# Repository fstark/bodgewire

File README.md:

# Bodgewire

A game about fixing old digital computers, chip by chip.

All the code in this repository was generated by Claude, Anthropic's AI, with a human telling it
what to build and checking the result. If you'd rather stay away from AI-made projects, this is
the place to stop reading. No hard feelings.

Try it in your browser: [fstark.github.io/bodgewire](https://fstark.github.io/bodgewire/).
Every Machine is there, slower than the desktop build (a fast computer helps), and without the
pop-out windows. It's not really playable that way, but it gives a good idea of what the game
looks like.

## The goal

Bodgewire simulates the repair of old digital computers: late-70s and early-80s boards made of
TTL chips, up to real 8-bit computers. Every signal on the board is simulated, so a fault is a
physical thing (a cracked trace, a chip output stuck low, a solder bridge) and the symptoms come
out of the circuit on their own. Nothing is scripted. Every fault has a cause, and you can find it.

## What it is

You're at a repair bench. In front of you is a broken Machine and a post-it saying what's wrong
with it: "The LED never lights." You have the board, its manuals (a User Manual, a Service Manual,
datasheets for every chip) and a shelf of real tools and instruments. Find the fault, fix it,
power it back on.

There are 125 Puzzles on 14 Machines. The first one blinks an LED with five chips. The last two
are chip-for-chip copies of the Commodore PET 2001 and the Sinclair ZX80, running their real ROMs.

Every Machine shows up in the launcher with a short description, and each of its Puzzles is a
post-it you can pick. "Start the Machine" gives you the working one, to see how it should behave.
A Puzzle you've repaired keeps its tick on the launcher, from one launch to the next.
The last post-it, "Random fault", breaks the Machine somewhere new each time you open it, and
checks that the fault shows before handing you the bench. It can be anywhere on the board, so
they never run out: fix one and the owner's card offers you another. If one beats you, the
binder's Give up page tells you what it was.

## A repair, step by step

Here's the Counter's first Puzzle, "Dark LED".

The bench opens on the board. Five 74LS161 counters divide a 1 MHz crystal down to about one blink
a second, and the red LED `D1` on the right should be blinking. It stays dark. The tools are on
the shelf at the bottom.

Hover a chip and its traces light up, with every pin named. On `U5`, pin 11 (`QD`) is the one that
goes to the LED.

So is the chip broken, or the LED, or something in between? Power off, take the multimeter, clip
its black lead on the LED's pad and hold the red one on `U5` pin 11. It shows dashes, no beep: a
trace runs from one to the other, but they aren't connected.

Zoom in on that trace. About halfway along, there's a hairline crack right across the copper.

A crack is a job for the soldering iron: click on it and a blob of solder bridges the gap. Power
back on, and the LED blinks.

Three seconds later the owner's card says thank you, with the next Puzzle one click away, and
the post-it gets a tick. The game checks the repair itself: the Board must now build the same
circuit as the fault-free one, whichever way you fixed it.

That one is easy. Later Puzzles hide the fault behind a TV picture that rolls, a keyboard that
types the wrong letters, or a BASIC that won't start.

## Tools and instruments

The shelf is the same on every Machine.

### Tools

- **Grease pencil**: mark the board with dots, checks and crosses, to keep track of what you've
  ruled out.
- **Chip puller**: swap a chip for a new one.
- **Soldering iron**: mend a cracked trace, resolder a chip pin.
- **Cutters**: cut a trace or a wire.
- **Bodge wire**: solder a wire between two pins.

Here the first four counters have been checked off, and the trace to the LED is the suspect:

### Instruments

- **Logic probe**: touch any copper and it tells you HIGH, LOW or PULSE.
- **Logic analyzer**: clip it on chip pins (its pin / bus switch takes a whole bus), set a
  trigger, and read what happened before and after it.
- **Oscilloscope**: four channels, for when the exact timing between signals matters.
- **Multimeter**: hold on copper; volts, or continuity with the power off.

The logic analyzer on the LED computer's 6502, triggered on its first instruction fetch. The
address and data buses read as values: the processor fetches its reset vector at FFFC and FFFD
(00, F8), jumps to F800 and starts running its program.

The oscilloscope on the Test Pattern Generator's video output: a pulse for each of the grid's
vertical lines, then the line's sync pulse below.

### The binder

Every Machine comes with its manuals, in a binder. The aA key on its cover makes the text larger,
in three steps, and it stays that way next time. The Service Manual explains the circuit, and
every chip and signal in it is a link to the board:

Each chip has its datasheet, with the pinout and what each pin is wired to on this board:

And you can look inside the memory chips: the BW-2001's ROM disassembled as 6502 code...

...or its character ROM, drawn glyph by glyph:

### And the rest

- **The post-it** with the Puzzle's symptom.
- **The Machine's own devices**: its TV, keyboard or paddle knobs, each in a window you can pop
  out to its own window on the desktop.
- **Controls**: power, pause / slow motion (a quarter of real time) / real time / as fast as
  possible, and Reset to undo every repair (your pencil marks stay).
- **View buttons** beside the Board: fit the whole Board, switch between the real and the plain
  look, pick the copper under the chips, hold a button or key down, flip the Board over.

The faults you'll meet are cracked traces, chip outputs stuck high or low, solder bridges, bad
joints, bad memory cells, the odd dead switch, and clocks running at the wrong speed.

## The Machines

### Counter

A red LED that blinks about once a second: half a second on, half a second off. The simplest board
on the bench. 4 Puzzles.

### LED Chaser

Eight red LEDs in a row, and one light running along them, about 15 steps a second. 5 Puzzles.

### Dice

Seven LEDs laid out like a die face. Hold the ROLL button and it rolls; let go and it lands on a
number from 1 to 6. 4 Puzzles.

### Stopwatch

Times things to a hundredth of a second, with START, STOP and RESET buttons, like the watch a coach
holds at the track. 9 Puzzles.

### Knob Meter

A paddle controller on a cable, and two digits showing how far its knob is turned, from 00 to 99.
8 Puzzles.

### Test Pattern Generator

The first board that drives a TV: a white grid on black, filling the screen. 8 Puzzles.

### Bouncing Ball

The first board that moves a picture: a square ball bouncing around a box, a dashed line down the
middle. 5 Puzzles.

### Paddle Tennis

Two players, two paddle knobs, a court seen from above, scores at the top. You know the one.
9 Puzzles.

### Message Display

A page of text on the TV, from a character ROM: the first verse of Emily Dickinson's "Hope" is the
thing with feathers. 7 Puzzles.

### TV Typewriter

A keyboard and a TV turned into a typewriter: what you type shows on the screen. It powers up full
of random characters until you press CLEAR. 7 Puzzles.

### LED computer

The first real computer on the bench: a 6502, a program in an EPROM, and a light bouncing back and
forth along eight LEDs. 7 Puzzles.

### BW-1

The first computer you can program yourself, built like the KIM-1 of 1976: type a program in on
the hex keypad, run it, stop it, step through it. 19 Puzzles.

### BW-2001

A copy of the Commodore PET 2001 of 1977, chip for chip and wire for wire, with the TV as its
screen and its keyboard in a window. It runs the original BASIC. 17 Puzzles.

### BW-80

A copy of the Sinclair ZX80 of 1980, chip for chip, programmed in BASIC on a TV. 16 Puzzles.

## Building it

You need git, CMake 3.28 or later, Ninja and clang: Apple's on a Mac, clang 23 on Linux. Clang is
the only compiler it's built with.

You also need a very powerful machine. Every chip is simulated signal by signal, and the big
computers are hungry: on an Apple M5 Max, the BW-2001 runs at a third of its real speed and the
BW-80 at a fifth. The small boards keep up in real time.

On a Mac:

```sh
xcode-select --install          # the compiler, if you don't have it yet
brew install cmake ninja
```

Then:

```sh
git clone https://github.com/fstark/bodgewire.git
cd bodgewire
cmake --preset release
cmake --build --preset release
build/release/src/ui/bw_ui
```

The first configure downloads SDL3, Dear ImGui and Catch2, so it needs the network once. The ROMs
the computers need are already in the repository. If you want to run the tests,
`ctest --preset release -j` takes a few minutes.

### Linux

It builds and runs on Ubuntu 24.04 with clang 23. The other things it needs:

```sh
sudo apt install git cmake ninja-build libstdc++-14-dev \
    libx11-dev libxext-dev libxrandr-dev libxcursor-dev libxi-dev libxkbcommon-dev \
    libwayland-dev libdecor-0-dev libasound2-dev libpulse-dev
```

Tell CMake to use clang on the first configure (it remembers after that):

```sh
git clone https://github.com/fstark/bodgewire.git
cd bodgewire
CC=clang-23 CXX=clang++-23 cmake --preset release
cmake --build --preset release
build/release/src/ui/bw_ui
```

It was tried on a very slow machine, an Intel i7-6700K from 2015. The small boards still keep up,
but Paddle Tennis runs at three quarters of its real speed, the BW-2001 at an eighth and the BW-80
at a twelfth.

On a Wayland desktop it runs through XWayland, so that an object can pop out into its own window.
To run it on Wayland itself, start it with `SDL_VIDEO_DRIVER=wayland`: everything then stays
inside the main window, as on the web.

If you run the tests with a KiCad older than 8 installed (Ubuntu's own is 7), the Board checks
(`drc_*`) fail. Without KiCad they're skipped.

It's developed on macOS. Windows hasn't been tried yet.

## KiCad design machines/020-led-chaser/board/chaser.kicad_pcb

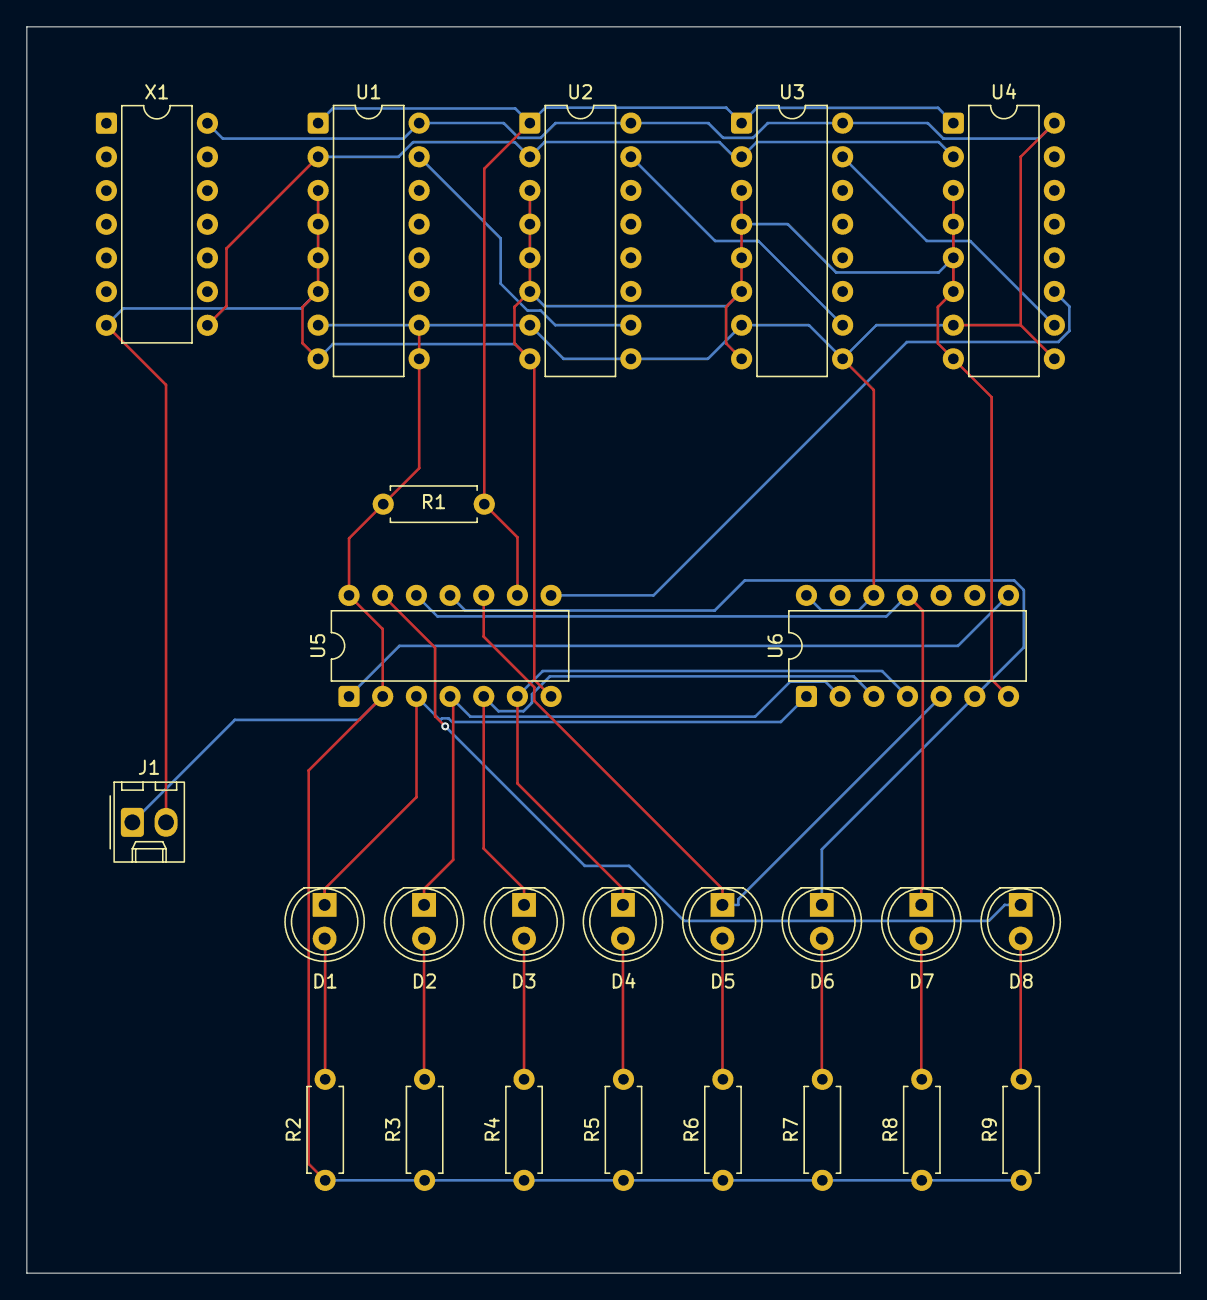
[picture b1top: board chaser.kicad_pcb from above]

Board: 2 copper layers, 87.0 x 94.0 mm, 25 parts (0 on the bottom side), 25 nets.

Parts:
D1, D2, D3, D4, D5, D6, D7, D8: LED; LED_D5.0mm
J1: POWER; Molex_KK-254_AE-6410-02A_1x02_P2.54mm_Vertical
R1: 4k7; R_Axial_DIN0207_L6.3mm_D2.5mm_P7.62mm_Horizontal
R2, R3, R4, R5, R6, R7, R8, R9: 330; R_Axial_DIN0207_L6.3mm_D2.5mm_P7.62mm_Horizontal
U1, U2, U3, U4: 74LS161; DIP-16_W7.62mm
U5: 74LS164; DIP-14_W7.62mm
U6: 74LS30; DIP-14_W7.62mm
X1: OSC; DIP-14_W7.62mm

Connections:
CARRY1: U1.15 (RCO), U2.10 (ENT)
CARRY2: U2.15 (RCO), U3.10 (ENT)
CARRY3: U3.15 (RCO), U4.10 (ENT)
CLK: U1.2 (CLK), U2.2 (CLK), U3.2 (CLK), U4.2 (CLK), X1.8 (OUT)
GND: J1.2 (GND), U1.3 (A), U1.4 (B), U1.5 (C), U1.6 (D), U1.8 (GND), U2.3 (A), U2.4 (B), U2.5 (C), U2.6 (D), U2.8 (GND), U3.3 (A), U3.4 (B), U3.5 (C), U3.6 (D), U3.8 (GND), U4.3 (A), U4.4 (B), U4.5 (C), U4.6 (D), U4.8 (GND), U5.7 (GND), U6.7 (GND), X1.7 (GND)
LED_A1: D1.2 (A), R2.2
LED_A2: D2.2 (A), R3.2
LED_A3: D3.2 (A), R4.2
LED_A4: D4.2 (A), R5.2
LED_A5: D5.2 (A), R6.2
LED_A6: D6.2 (A), R7.2
LED_A7: D7.2 (A), R8.2
LED_A8: D8.2 (A), R9.2
RESET_N: R1.2, U1.1 (CLR_N), U2.1 (CLR_N), U3.1 (CLR_N), U4.1 (CLR_N), U5.9 (CLR_N)
S1: D1.1 (K), U5.3 (QA), U6.1 (A)
S2: D2.1 (K), U5.4 (QB), U6.2 (B)
S3: D3.1 (K), U5.5 (QC), U6.3 (C)
S4: D4.1 (K), U5.6 (QD), U6.4 (D)
S5: D5.1 (K), U5.10 (QE), U6.5 (E)
S6: D6.1 (K), U5.11 (QF), U6.6 (F)
S7: D7.1 (K), U5.12 (QG), U6.11 (G)
S8: D8.1 (K), U5.13 (QH)
SER: U5.1 (A), U6.8 (Y)
STEP: U4.11 (QD), U5.8 (CLK)
VCC: J1.1 (VCC), R1.1, R2.1, R3.1, R4.1, R5.1, R6.1, R7.1, R8.1, R9.1, U1.7 (ENP), U1.9 (LOAD_N), U1.10 (ENT), U1.16 (VCC), U2.7 (ENP), U2.9 (LOAD_N), U2.16 (VCC), U3.7 (ENP), U3.9 (LOAD_N), U3.16 (VCC), U4.7 (ENP), U4.9 (LOAD_N), U4.16 (VCC), U5.2 (B), U5.14 (VCC), U6.12 (H), U6.14 (VCC), X1.14 (VCC)

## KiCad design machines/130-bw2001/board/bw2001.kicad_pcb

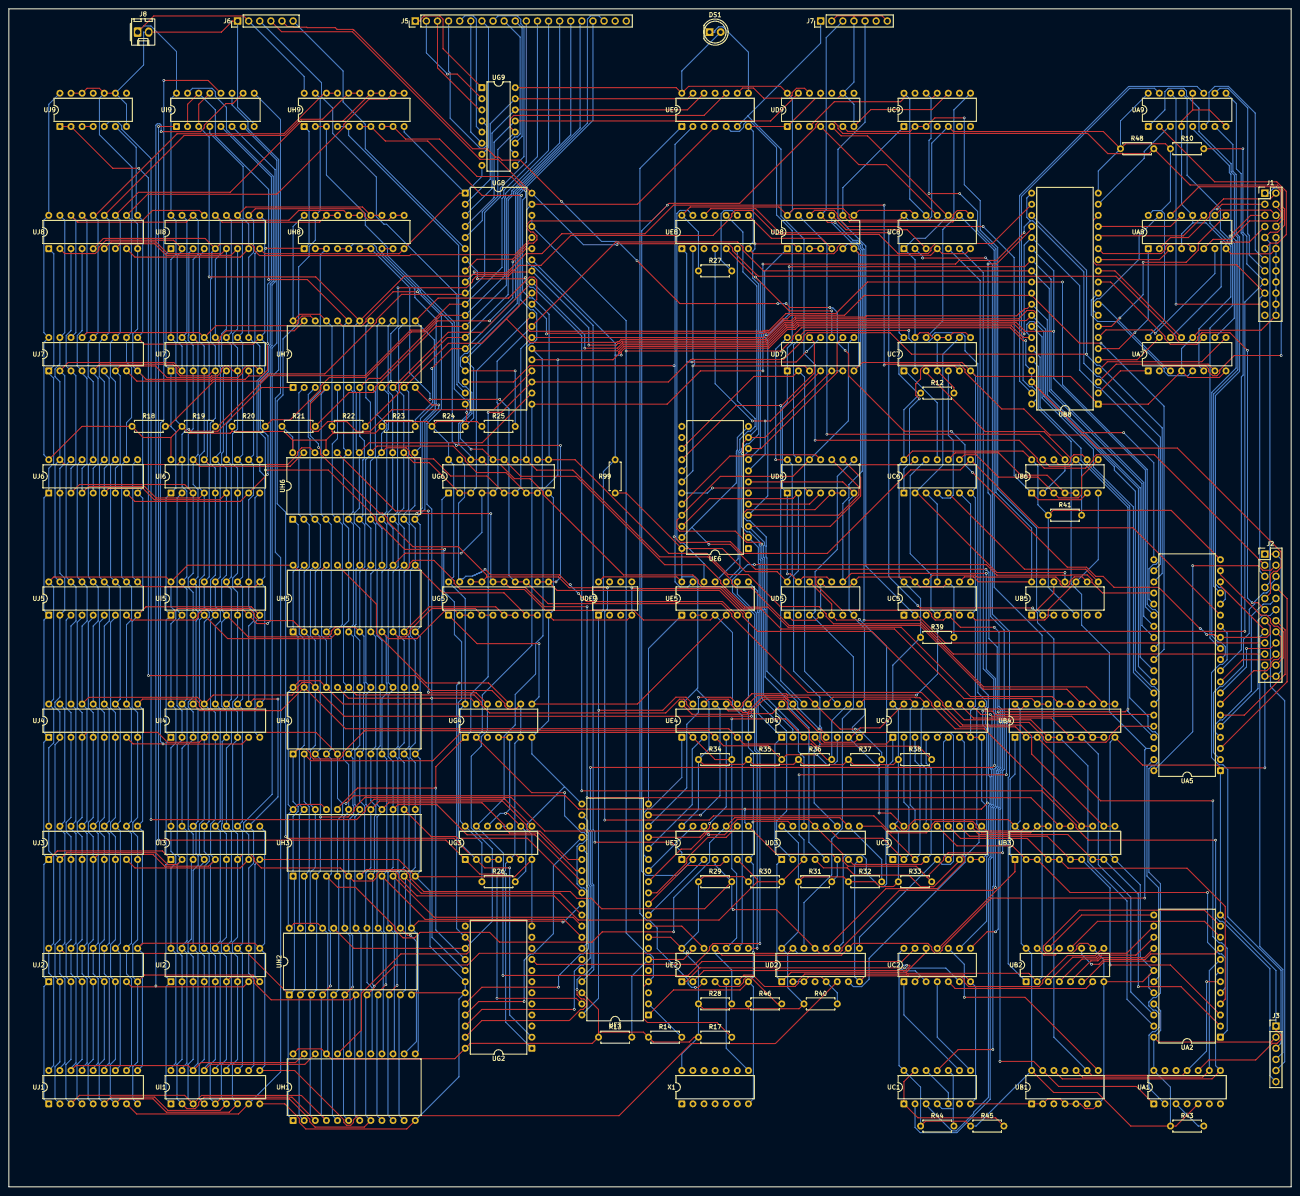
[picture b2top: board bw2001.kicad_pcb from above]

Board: 2 copper layers, 293.3 x 269.4 mm, 117 parts (0 on the bottom side), 278 nets.

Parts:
DS1: LED; LED_D5.0mm
J1: IEEE488; PinHeader_2x12_P2.54mm_Vertical
J2: USERPORT; PinHeader_2x12_P2.54mm_Vertical
J3, J6: CASSETTE; PinHeader_1x06_P2.54mm_Vertical
J5: BW2001KB; PinHeader_1x20_P2.54mm_Vertical
J7: MONITOR; PinHeader_1x07_P2.54mm_Vertical
J8: POWER; Molex_KK-254_AE-6410-02A_1x02_P2.54mm_Vertical
R10, R48: 2k4; R_Axial_DIN0207_L6.3mm_D2.5mm_P7.62mm_Horizontal
R12, R13, R14, R26, R27, R28, R29, R30, R31, R32, R33, R34, R35, R36, R37, R38, R39, R40, R41, R43, R44, R45, R46: 1k; R_Axial_DIN0207_L6.3mm_D2.5mm_P7.62mm_Horizontal
R17, R99: 3k3; R_Axial_DIN0207_L6.3mm_D2.5mm_P7.62mm_Horizontal
R18, R19, R20, R21, R22, R23, R24, R25: 10k; R_Axial_DIN0207_L6.3mm_D2.5mm_P7.62mm_Horizontal
UA1: 74LS93; DIP-14_W7.62mm
UA2: 2316B; DIP-24_W15.24mm
UA5: 6522; DIP-40_W15.24mm
UA7, UA8, UA9: MC3446; DIP-16_W7.62mm
UB1: 74LS20; DIP-14_W7.62mm
UB2: 74LS165; DIP-16_W7.62mm
UB3, UB4: 74LS244; DIP-20_W7.62mm
UB5: 74LS93; DIP-14_W7.62mm
UB6: 74LS107; DIP-14_W7.62mm
UB8: 6520; DIP-40_W15.24mm
UC1: 74LS74; DIP-14_W7.62mm
UC2: 74LS00; DIP-14_W7.62mm
UC3, UC4: 2114; DIP-18_W7.62mm
UC5, UC7, UC8: 74LS107; DIP-14_W7.62mm
UC6: 74LS08; DIP-14_W7.62mm
UC9: 74LS93; DIP-14_W7.62mm
UD2, UD3, UD4: 74LS157; DIP-16_W7.62mm
UD5: 74LS107; DIP-14_W7.62mm
UD6, UD7: 74177; DIP-14_W7.62mm
UD8: 74LS00; DIP-14_W7.62mm
UD9: 74LS04; DIP-14_W7.62mm
UDE9: POR; DIP-8_W7.62mm
UE2: 74LS08; DIP-14_W7.62mm
UE3, UE4: 7417; DIP-14_W7.62mm
UE5: 74LS04; DIP-14_W7.62mm
UE6: 74100; DIP-24_W15.24mm
UE8, UE9: 74LS20; DIP-14_W7.62mm
UF3: 6502; DIP-40_W15.24mm
UG2: 74LS154; DIP-24_W15.24mm
UG3: 74LS00; DIP-14_W7.62mm
UG4: 74LS21; DIP-14_W7.62mm
UG5, UG6: 74LS244; DIP-20_W7.62mm
UG8: 6520; DIP-40_W15.24mm
UG9: 74LS145; DIP-16_W7.62mm
UH1, UH2, UH3, UH4, UH5, UH6, UH7: 2316B; DIP-24_W15.24mm
UH8, UH9: 74LS244; DIP-20_W7.62mm
UI1, UI2, UI3, UI4, UI5, UI6, UI7, UI8: 2114; DIP-18_W7.62mm
UI9: 74LS139; DIP-16_W7.62mm
UJ1, UJ2, UJ3, UJ4, UJ5, UJ6, UJ7, UJ8: 2114; DIP-18_W7.62mm
UJ9: 74LS00; DIP-14_W7.62mm
X1: OSC; DIP-14_W7.62mm

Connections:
A0: UE2.12 (4A), UF3.9 (A0)
A1: UE3.3 (2A), UF3.10 (A1)
A2: UE3.5 (3A), UF3.11 (A2)
A3: UE3.9 (4A), UF3.12 (A3)
A4: UE3.11 (5A), UF3.13 (A4)
A5: UE3.13 (6A), UF3.14 (A5)
A6: UE4.1 (1A), UF3.15 (A6)
A7: UE4.3 (2A), UF3.16 (A7)
A8: UE4.5 (3A), UF3.17 (A8)
A9: UE4.9 (4A), UF3.18 (A9)
A10: UE4.11 (5A), UF3.19 (A10)
A11: UE5.1 (1A), UF3.20 (A11)
A12: UF3.22 (A12), UG2.23 (A)
A13: UF3.23 (A13), UG2.22 (B)
A14: UF3.24 (A14), UG2.21 (C)
A15: UF3.25 (A15), UG2.20 (D)
ATN_IN_N: UA9.15 (RD), UB8.40 (CA1)
ATN_N: J1.21 (ATN_N), UA9.14 (BUSD)
ATN_OUT_N: UA5.12 (PB2), UA9.13 (DD)
BA0: R28.2, UA5.38 (RS0), UB8.36 (RS0), UD2.10 (3B), UE2.11 (4Y), UG8.36 (RS0), UH1.8 (A0), UH2.8 (A0), UH3.8 (A0), UH4.8 (A0), UH5.8 (A0), UH6.8 (A0), UH7.8 (A0), UI1.5 (A0), UI2.5 (A0), UI3.5 (A0), UI4.5 (A0), UI5.5 (A0), UI6.5 (A0), UI7.5 (A0), UI8.5 (A0), UJ1.5 (A0), UJ2.5 (A0), UJ3.5 (A0), UJ4.5 (A0), UJ5.5 (A0), UJ6.5 (A0), UJ7.5 (A0), UJ8.5 (A0)
BA1: R29.2, UA5.37 (RS1), UB8.35 (RS1), UD2.13 (4B), UE3.4 (2Y), UG8.35 (RS1), UH1.7 (A1), UH2.7 (A1), UH3.7 (A1), UH4.7 (A1), UH5.7 (A1), UH6.7 (A1), UH7.7 (A1), UI1.6 (A1), UI2.6 (A1), UI3.6 (A1), UI4.6 (A1), UI5.6 (A1), UI6.6 (A1), UI7.6 (A1), UI8.6 (A1), UJ1.6 (A1), UJ2.6 (A1), UJ3.6 (A1), UJ4.6 (A1), UJ5.6 (A1), UJ6.6 (A1), UJ7.6 (A1), UJ8.6 (A1)
BA2: R30.2, UA5.36 (RS2), UD3.3 (1B), UE3.6 (3Y), UH1.6 (A2), UH2.6 (A2), UH3.6 (A2), UH4.6 (A2), UH5.6 (A2), UH6.6 (A2), UH7.6 (A2), UI1.7 (A2), UI2.7 (A2), UI3.7 (A2), UI4.7 (A2), UI5.7 (A2), UI6.7 (A2), UI7.7 (A2), UI8.7 (A2), UJ1.7 (A2), UJ2.7 (A2), UJ3.7 (A2), UJ4.7 (A2), UJ5.7 (A2), UJ6.7 (A2), UJ7.7 (A2), UJ8.7 (A2)
BA3: R31.2, UA5.35 (RS3), UD3.6 (2B), UE3.8 (4Y), UH1.5 (A3), UH2.5 (A3), UH3.5 (A3), UH4.5 (A3), UH5.5 (A3), UH6.5 (A3), UH7.5 (A3), UI1.4 (A3), UI2.4 (A3), UI3.4 (A3), UI4.4 (A3), UI5.4 (A3), UI6.4 (A3), UI7.4 (A3), UI8.4 (A3), UJ1.4 (A3), UJ2.4 (A3), UJ3.4 (A3), UJ4.4 (A3), UJ5.4 (A3), UJ6.4 (A3), UJ7.4 (A3), UJ8.4 (A3)
BA4: R32.2, UD3.10 (3B), UE3.10 (5Y), UG8.24 (CS1), UH1.4 (A4), UH2.4 (A4), UH3.4 (A4), UH4.4 (A4), UH5.4 (A4), UH6.4 (A4), UH7.4 (A4), UI1.3 (A4), UI2.3 (A4), UI3.3 (A4), UI4.3 (A4), UI5.3 (A4), UI6.3 (A4), UI7.3 (A4), UI8.3 (A4), UJ1.3 (A4), UJ2.3 (A4), UJ3.3 (A4), UJ4.3 (A4), UJ5.3 (A4), UJ6.3 (A4), UJ7.3 (A4), UJ8.3 (A4)
BA5: R33.2, UB8.24 (CS1), UD3.13 (4B), UE3.12 (6Y), UH1.3 (A5), UH2.3 (A5), UH3.3 (A5), UH4.3 (A5), UH5.3 (A5), UH6.3 (A5), UH7.3 (A5), UI1.2 (A5), UI2.2 (A5), UI3.2 (A5), UI4.2 (A5), UI5.2 (A5), UI6.2 (A5), UI7.2 (A5), UI8.2 (A5), UJ1.2 (A5), UJ2.2 (A5), UJ3.2 (A5), UJ4.2 (A5), UJ5.2 (A5), UJ6.2 (A5), UJ7.2 (A5), UJ8.2 (A5)
BA6: R34.2, UD4.3 (1B), UE2.10 (3B), UE4.2 (1Y), UH1.2 (A6), UH2.2 (A6), UH3.2 (A6), UH4.2 (A6), UH5.2 (A6), UH6.2 (A6), UH7.2 (A6), UI1.1 (A6), UI2.1 (A6), UI3.1 (A6), UI4.1 (A6), UI5.1 (A6), UI6.1 (A6), UI7.1 (A6), UI8.1 (A6), UJ1.1 (A6), UJ2.1 (A6), UJ3.1 (A6), UJ4.1 (A6), UJ5.1 (A6), UJ6.1 (A6), UJ7.1 (A6), UJ8.1 (A6)
BA7: R35.2, UD4.6 (2B), UE4.4 (2Y), UH1.1 (A7), UH2.1 (A7), UH3.1 (A7), UH4.1 (A7), UH5.1 (A7), UH6.1 (A7), UH7.1 (A7), UI1.17 (A7), UI2.17 (A7), UI3.17 (A7), UI4.17 (A7), UI5.17 (A7), UI6.17 (A7), UI7.17 (A7), UI8.17 (A7), UJ1.17 (A7), UJ2.17 (A7), UJ3.17 (A7), UJ4.17 (A7), UJ5.17 (A7), UJ6.17 (A7), UJ7.17 (A7), UJ8.17 (A7)
BA8: R36.2, UD4.10 (3B), UE4.6 (3Y), UH1.23 (A8), UH2.23 (A8), UH3.23 (A8), UH4.23 (A8), UH5.23 (A8), UH6.23 (A8), UH7.23 (A8), UI1.16 (A8), UI2.16 (A8), UI3.16 (A8), UI4.16 (A8), UI5.16 (A8), UI6.16 (A8), UI7.16 (A8), UI8.16 (A8), UJ1.16 (A8), UJ2.16 (A8), UJ3.16 (A8), UJ4.16 (A8), UJ5.16 (A8), UJ6.16 (A8), UJ7.16 (A8), UJ8.16 (A8)
BA9: R37.2, UD4.13 (4B), UE4.8 (4Y), UH1.22 (A9), UH2.22 (A9), UH3.22 (A9), UH4.22 (A9), UH5.22 (A9), UH6.22 (A9), UH7.22 (A9), UI1.15 (A9), UI2.15 (A9), UI3.15 (A9), UI4.15 (A9), UI5.15 (A9), UI6.15 (A9), UI7.15 (A9), UI8.15 (A9), UJ1.15 (A9), UJ2.15 (A9), UJ3.15 (A9), UJ4.15 (A9), UJ5.15 (A9), UJ6.15 (A9), UJ7.15 (A9), UJ8.15 (A9)
BA10: R38.2, UE4.10 (5Y), UH1.19 (A10), UH2.19 (A10), UH3.19 (A10), UH4.19 (A10), UH5.19 (A10), UH6.19 (A10), UH7.19 (A10), UI9.2 (1A), UI9.14 (2A)
BA11: UB8.22 (CS0), UE2.9 (3A), UE5.4 (2Y), UG8.22 (CS0), UH1.18 (CS2), UH2.18 (CS2), UH3.18 (CS2), UH4.18 (CS2), UH5.18 (CS2), UH6.18 (CS2), UH7.18 (CS2), UI9.3 (1B), UI9.13 (2B)
BA11_N: UE5.2 (1Y), UE5.3 (2A)
BBD0: UH8.17 (2A4), UH8.18 (1Y1), UI1.14 (IO1), UI2.14 (IO1), UI3.14 (IO1), UI4.14 (IO1), UI5.14 (IO1), UI6.14 (IO1), UI7.14 (IO1), UI8.14 (IO1)
BBD1: UH8.15 (2A3), UH8.16 (1Y2), UI1.13 (IO2), UI2.13 (IO2), UI3.13 (IO2), UI4.13 (IO2), UI5.13 (IO2), UI6.13 (IO2), UI7.13 (IO2), UI8.13 (IO2)
BBD2: UH8.13 (2A2), UH8.14 (1Y3), UI1.12 (IO3), UI2.12 (IO3), UI3.12 (IO3), UI4.12 (IO3), UI5.12 (IO3), UI6.12 (IO3), UI7.12 (IO3), UI8.12 (IO3)
BBD3: UH8.11 (2A1), UH8.12 (1Y4), UI1.11 (IO4), UI2.11 (IO4), UI3.11 (IO4), UI4.11 (IO4), UI5.11 (IO4), UI6.11 (IO4), UI7.11 (IO4), UI8.11 (IO4)
BBD4: UH9.17 (2A4), UH9.18 (1Y1), UJ1.14 (IO1), UJ2.14 (IO1), UJ3.14 (IO1), UJ4.14 (IO1), UJ5.14 (IO1), UJ6.14 (IO1), UJ7.14 (IO1), UJ8.14 (IO1)
BBD5: UH9.15 (2A3), UH9.16 (1Y2), UJ1.13 (IO2), UJ2.13 (IO2), UJ3.13 (IO2), UJ4.13 (IO2), UJ5.13 (IO2), UJ6.13 (IO2), UJ7.13 (IO2), UJ8.13 (IO2)
BBD6: UH9.13 (2A2), UH9.14 (1Y3), UJ1.12 (IO3), UJ2.12 (IO3), UJ3.12 (IO3), UJ4.12 (IO3), UJ5.12 (IO3), UJ6.12 (IO3), UJ7.12 (IO3), UJ8.12 (IO3)
BBD7: UH9.11 (2A1), UH9.12 (1Y4), UJ1.11 (IO4), UJ2.11 (IO4), UJ3.11 (IO4), UJ4.11 (IO4), UJ5.11 (IO4), UJ6.11 (IO4), UJ7.11 (IO4), UJ8.11 (IO4)
BD0: UB3.17 (2A4), UB3.18 (1Y1), UG5.17 (2A4), UG5.18 (1Y1), UH8.2 (1A1), UH8.3 (2Y4)
BD1: UB3.15 (2A3), UB3.16 (1Y2), UG5.15 (2A3), UG5.16 (1Y2), UH8.4 (1A2), UH8.5 (2Y3)
BD2: UB3.13 (2A2), UB3.14 (1Y3), UG5.13 (2A2), UG5.14 (1Y3), UH8.6 (1A3), UH8.7 (2Y2)
BD3: UB3.11 (2A1), UB3.12 (1Y4), UG5.11 (2A1), UG5.12 (1Y4), UH8.8 (1A4), UH8.9 (2Y1)
BD4: UB4.17 (2A4), UB4.18 (1Y1), UG6.17 (2A4), UG6.18 (1Y1), UH9.2 (1A1), UH9.3 (2Y4)
BD5: UB4.15 (2A3), UB4.16 (1Y2), UG6.15 (2A3), UG6.16 (1Y2), UH9.4 (1A2), UH9.5 (2Y3)
BD6: UB4.13 (2A2), UB4.14 (1Y3), UG6.13 (2A2), UG6.14 (1Y3), UH9.6 (1A3), UH9.7 (2Y2)
BD7: UB4.11 (2A1), UB4.12 (1Y4), UG6.11 (2A1), UG6.12 (1Y4), UH9.8 (1A4), UH9.9 (2Y1)
BD_TO_D: UE5.5 (3A), UG4.8 (2Y), UG5.1 (1OE_N), UG6.1 (1OE_N)
BD_TO_D_N: UE5.6 (3Y), UG5.19 (2OE_N), UG6.19 (2OE_N)
BLANK_TV: UE3.1 (1A), UE9.4 (1C), UG8.39 (CA2)
BLKEND_N: UD8.5 (2B), UE8.8 (2Y)
BPHI2: UG3.8 (3Y), UJ9.5 (2B)
CASS1_MOTOR: J6.3 (MOTOR), UG8.19 (CB2)
CASS1_READ: J2.11 (READ1), J6.4 (READ), UG8.40 (CA1)
CASS1_SWITCH: J6.6 (SENSE), UG8.6 (PA4)
CASS2_MOTOR: J3.3 (MOTOR), UA5.14 (PB4)
CASS2_READ: J2.15 (READ2), J3.4 (READ), UA5.18 (CB1)
CASS2_SWITCH: J3.6 (SENSE), UG8.7 (PA5)
CASS_WRITE: J2.13 (WRITE), J3.5 (WRITE), J6.5 (WRITE), UA5.13 (PB3)
CD0: UA2.9 (O0), UB2.11 (A)
CD1: UA2.10 (O1), UB2.12 (B)
CD2: UA2.11 (O2), UB2.13 (C)
CD3: UA2.13 (O3), UB2.14 (D)
CD4: UA2.14 (O4), UB2.3 (E)
CD5: UA2.15 (O5), UB2.4 (F)
CD6: UA2.16 (O6), UB2.5 (G)
CD7: UA2.17 (O7), UB2.6 (H)
CHLOAD: UC1.11 (2CLK), UC8.3 (1Q), UD5.9 (2CLK), UD8.10 (3B)
CHLOAD_CLR_N: UC8.13 (1CLR_N), UD8.8 (3Y)
CHLOAD_N: UB2.1 (SH_LD_N), UC8.2 (1Q_N)
CLK1M: UC8.8 (2J), UC8.12 (1CLK), UC9.11 (QD), UC9.14 (CKA), UD9.3 (2A)
CLK1M_N: UC8.11 (2K), UD9.4 (2Y)
CLK2M: UC7.12 (1CLK), UC9.8 (QC)
CLK8: UB2.2 (CLK), UC8.9 (2CLK), UC9.1 (CKB), UD8.9 (3A), UE2.6 (2Y)
D0: UA5.33 (D0), UB8.33 (D0), UF3.33 (D0), UG5.2 (1A1), UG5.3 (2Y4), UG8.33 (D0), UH1.9 (O0), UH2.9 (O0), UH3.9 (O0), UH4.9 (O0), UH5.9 (O0), UH6.9 (O0), UH7.9 (O0)
D1: UA5.32 (D1), UB8.32 (D1), UF3.32 (D1), UG5.4 (1A2), UG5.5 (2Y3), UG8.32 (D1), UH1.10 (O1), UH2.10 (O1), UH3.10 (O1), UH4.10 (O1), UH5.10 (O1), UH6.10 (O1), UH7.10 (O1)
D2: UA5.31 (D2), UB8.31 (D2), UF3.31 (D2), UG5.6 (1A3), UG5.7 (2Y2), UG8.31 (D2), UH1.11 (O2), UH2.11 (O2), UH3.11 (O2), UH4.11 (O2), UH5.11 (O2), UH6.11 (O2), UH7.11 (O2)
D3: UA5.30 (D3), UB8.30 (D3), UF3.30 (D3), UG5.8 (1A4), UG5.9 (2Y1), UG8.30 (D3), UH1.13 (O3), UH2.13 (O3), UH3.13 (O3), UH4.13 (O3), UH5.13 (O3), UH6.13 (O3), UH7.13 (O3)
D4: UA5.29 (D4), UB8.29 (D4), UF3.29 (D4), UG6.2 (1A1), UG6.3 (2Y4), UG8.29 (D4), UH1.14 (O4), UH2.14 (O4), UH3.14 (O4), UH4.14 (O4), UH5.14 (O4), UH6.14 (O4), UH7.14 (O4)
D5: UA5.28 (D5), UB8.28 (D5), UF3.28 (D5), UG6.4 (1A2), UG6.5 (2Y3), UG8.28 (D5), UH1.15 (O5), UH2.15 (O5), UH3.15 (O5), UH4.15 (O5), UH5.15 (O5), UH6.15 (O5), UH7.15 (O5)
D6: UA5.27 (D6), UB8.27 (D6), UF3.27 (D6), UG6.6 (1A3), UG6.7 (2Y2), UG8.27 (D6), UH1.16 (O6), UH2.16 (O6), UH3.16 (O6), UH4.16 (O6), UH5.16 (O6), UH6.16 (O6), UH7.16 (O6)
D7: UA5.26 (D7), UB8.26 (D7), UF3.26 (D7), UG6.8 (1A4), UG6.9 (2Y1), UG8.26 (D7), UH1.17 (O7), UH2.17 (O7), UH3.17 (O7), UH4.17 (O7), UH5.17 (O7), UH6.17 (O7), UH7.17 (O7)
DAV_IN_N: UA5.17 (PB7), UA9.1 (RA)
DAV_N: J1.11 (DAV_N), UA9.2 (BUSA)
DAV_OUT_N: UA9.3 (DA), UB8.19 (CB2)
DI1: UA7.1 (RA), UB8.2 (PA0)
DI2: UA7.7 (RB), UB8.3 (PA1)
DI3: UA7.9 (RC), UB8.4 (PA2)
DI4: UA7.15 (RD), UB8.5 (PA3)
DI5: UA8.1 (RA), UB8.6 (PA4)
DI6: UA8.7 (RB), UB8.7 (PA5)
DI7: UA8.9 (RC), UB8.8 (PA6)
DI8: UA8.15 (RD), UB8.9 (PA7)
DIAG: J2.9 (DIAG), UG8.9 (PA7)
DIAG_LED_N: DS1.1 (K), UE9.8 (2Y)
DIO1: J1.1 (DIO1), UA7.2 (BUSA)
DIO2: J1.3 (DIO2), UA7.6 (BUSB)
DIO3: J1.5 (DIO3), UA7.10 (BUSC)
DIO4: J1.7 (DIO4), UA7.14 (BUSD)
DIO5: J1.2 (DIO5), UA8.2 (BUSA)
DIO6: J1.4 (DIO6), UA8.6 (BUSB)
DIO7: J1.6 (DIO7), UA8.10 (BUSC)
DIO8: J1.8 (DIO8), UA8.14 (BUSD)
DISON_CLR: UC5.11 (2K), UC6.3 (1Y)
DISON_SET: UC5.8 (2J), UC6.6 (2Y)
DIS_OFF: UC5.4 (1K), UC5.6 (2Q_N), UC6.12 (4A)
DIS_ON: UA1.1 (CKB), UB1.13 (2D), UC5.1 (1J), UC5.5 (2Q), UD5.10 (2CLR_N), UD5.13 (1CLR_N), UD6.1 (CT_LOAD_N), UD7.1 (CT_LOAD_N), UE9.5 (1D)
DO1: UA7.3 (DA), UB8.10 (PB0)
DO2: UA7.5 (DB), UB8.11 (PB1)
DO3: UA7.11 (DC), UB8.12 (PB2)
DO4: UA7.13 (DD), UB8.13 (PB3)
DO5: UA8.3 (DA), UB8.14 (PB4)
DO6: UA8.5 (DB), UB8.15 (PB5)
DO7: UA8.11 (DC), UB8.16 (PB6)
DO8: UA8.13 (DD), UB8.17 (PB7)
DOT: UB2.9 (QH), UC2.2 (1B)
DOT_N: UB2.7 (QH_N), UC2.5 (2B)
END25_N: UD8.3 (1Y), UD8.4 (2A)
EOI_N: J1.9 (EOI_N), J2.7 (EOI_N), R48.2, UE3.2 (1Y), UG8.8 (PA6)
G3_11: UG3.10 (3B), UG3.11 (4Y)
GND: J1.10 (REN), J1.12 (GND1), J1.14 (GND2), J1.16 (GND3), J1.18 (GND4), J1.20 (GND5), J1.22 (GND6), J1.24 (GND7), J2.1 (GND1), J2.2 (GND4), J2.21 (GND2), J2.23 (GND3), J2.24 (GND5), J3.1 (GND), J6.1 (GND), J7.2 (GND1), J7.4 (GND2), J7.7 (GND3), J8.2 (GND), UA1.10 (GND), UA2.12 (GND), UA2.18 (CS2), UA2.20 (CS1), UA5.1 (GND), UA7.4 (ENABC_N), UA7.8 (GND), UA7.12 (END_N), UA8.4 (ENABC_N), UA8.8 (GND), UA8.12 (END_N), UA9.4 (ENABC_N), UA9.8 (GND), UA9.12 (END_N), UB1.1 (1A), UB1.2 (1B), UB1.4 (1C), UB1.5 (1D), UB1.7 (GND), UB2.8 (GND), UB2.10 (SER), UB2.15 (CLK_INH), UB3.10 (GND), UB4.10 (GND), UB5.10 (GND), UB6.7 (GND), UB8.1 (GND), UC1.7 (GND), UC2.7 (GND), UC3.8 (CS_N), UC3.9 (GND), UC4.8 (CS_N), UC4.9 (GND), UC5.7 (GND), UC6.7 (GND), UC7.7 (GND), UC8.4 (1K), UC8.7 (GND), UC9.10 (GND), UD2.8 (GND), UD2.15 (G_N), UD3.8 (GND), UD3.15 (G_N), UD4.8 (GND), UD4.15 (G_N), UD5.7 (GND), UD6.7 (GND), UD7.7 (GND), UD8.7 (GND), UD9.1 (1A), UD9.7 (GND), UD9.9 (4A), UD9.11 (5A), UDE9.4 (GND), UE2.7 (GND), UE3.7 (GND), UE4.7 (GND), UE5.7 (GND), UE6.7 (GND), UE8.7 (GND), UE9.7 (GND), UF3.1 (GND), UF3.21 (GND2), UG2.12 (GND), UG2.18 (G1_N), UG2.19 (G2_N), UG3.7 (GND), UG4.7 (GND), UG5.10 (GND), UG6.10 (GND), UG8.1 (GND), UG9.8 (GND), UH1.12 (GND), UH2.12 (GND), UH3.12 (GND), UH4.12 (GND), UH5.12 (GND), UH6.12 (GND), UH7.12 (GND), UH8.10 (GND), UH9.10 (GND), UI1.9 (GND), UI2.9 (GND), UI3.9 (GND), UI4.9 (GND), UI5.9 (GND), UI6.9 (GND), UI7.9 (GND), UI8.9 (GND), UI9.8 (GND), UJ1.9 (GND), UJ2.9 (GND), UJ3.9 (GND), UJ4.9 (GND), UJ5.9 (GND), UJ6.9 (GND), UJ7.9 (GND), UJ8.9 (GND), UJ9.7 (GND), UJ9.9 (3A), UJ9.10 (3B), UJ9.12 (4A), UJ9.13 (4B), X1.7 (GND)
GRAPHIC: UA2.19 (A10), UA5.39 (CA2)
H0: UB5.14 (CKA), UC5.9 (2CLK), UC9.12 (QA)
H1: UB5.1 (CKB), UB5.12 (QA)
H2: UB5.9 (QB), UC5.12 (1CLK)
H3: UB5.8 (QC), UC6.5 (2B)
H4: UB5.11 (QD), UC6.2 (1B), UC7.9 (2CLK)
H5: UC6.4 (2A), UC7.5 (2Q)
H5_N: UC6.1 (1A), UC7.6 (2Q_N)
HCNT_CLR: UB5.2 (R01), UB5.3 (R02), UC9.2 (R01), UC9.3 (R02), UD9.6 (3Y)
HORZ_DRIVE: J2.17 (HORZ), J7.5 (HDRIVE), UC5.2 (1Q_N)
IFC_N: J1.17 (IFC_N), R10.2, UE4.12 (6Y)
IRQ_N: R17.2, UA5.21 (IRQ_N), UB8.37 (IRQB_N), UB8.38 (IRQA_N), UF3.4 (IRQ_N), UG8.37 (IRQB_N), UG8.38 (IRQA_N)
KEY_A: UE9.13 (2D), UG8.2 (PA0), UG9.15 (A)
KEY_B: UE9.12 (2C), UG8.3 (PA1), UG9.14 (B)
KEY_C: UD9.13 (6A), UG8.4 (PA2), UG9.13 (C)
KEY_C_N: UD9.12 (6Y), UE9.9 (2A)
KEY_D: UE9.10 (2B), UG8.5 (PA3), UG9.12 (D)
KIN0: J5.11 (COL0), R18.2, UG8.10 (PB0)
KIN1: J5.12 (COL1), R19.2, UG8.11 (PB1)
KIN2: J5.13 (COL2), R20.2, UG8.12 (PB2)
KIN3: J5.14 (COL3), R21.2, UG8.13 (PB3)
KIN4: J5.15 (COL4), R22.2, UG8.14 (PB4)
KIN5: J5.16 (COL5), R23.2, UG8.15 (PB5)
KIN6: J5.17 (COL6), R24.2, UG8.16 (PB6)
KIN7: J5.18 (COL7), R25.2, UG8.17 (PB7)
LA2: UD6.4 (A), UE6.5 (1Q1)
LA3: UD6.10 (B), UD8.1 (1A), UE6.4 (1Q2)
LA4: UD6.3 (C), UE6.19 (1Q3)
LA5: UD6.11 (D), UE6.20 (1Q4)
LA6: UD7.4 (A), UE6.8 (2Q1), UE8.4 (1C)
LA7: UD7.10 (B), UE6.9 (2Q2), UE8.5 (1D)
LA8: UD7.3 (C), UE6.18 (2Q3), UE8.2 (1B)
LA9: UD7.11 (D), UE6.17 (2Q4), UE8.1 (1A)
LATCH_G: UC2.8 (3Y), UE6.12 (2G), UE6.23 (1G)
LAT_HI: UD8.2 (1B), UE5.10 (5Y)
LAT_HI_N: UE5.11 (5A), UE8.6 (1Y)
NDAC_IN_N: UA5.10 (PB0), UA9.9 (RC)
NDAC_N: J1.15 (NDAC_N), UA9.10 (BUSC)
NDAC_OUT_N: UA9.11 (DC), UB8.39 (CA2)
NMI_N: R13.2, UE2.13 (4B), UF3.6 (NMI_N)
NRFD_IN_N: UA5.16 (PB6), UA9.7 (RB)
NRFD_N: J1.13 (NRFD_N), UA9.6 (BUSB)
NRFD_OUT_N: UA5.11 (PB1), UA9.5 (DB)
OSC8: UE2.5 (2B), X1.8 (OUT)
PA0: J2.6 (PA0), UA5.2 (PA0)
PA1: J2.8 (PA1), UA5.3 (PA1)
PA2: J2.10 (PA2), UA5.4 (PA2)
PA3: J2.12 (PA3), UA5.5 (PA3)
PA4: J2.14 (PA4), UA5.6 (PA4)
PA5: J2.16 (PA5), UA5.7 (PA5)
PA6: J2.18 (PA6), UA5.8 (PA6)
PA7: J2.20 (PA7), UA5.9 (PA7)
PHI0: UC8.6 (2Q_N), UF3.37 (PHI0)
PHI0_N: UC1.3 (1CLK), UC8.5 (2Q)
PHI2: UA5.25 (PHI2), UB8.25 (PHI2), UF3.39 (PHI2), UG3.13 (4B), UG8.25 (PHI2)
PIXEL: UE2.3 (1Y), UE9.1 (1A)
PIX_A_N: UC2.3 (1Y), UE2.2 (1B)
PIX_B_N: UC2.6 (2Y), UE2.1 (1A)
PU_R12: R12.2, UC7.4 (1K), UC7.8 (2J), UC7.10 (2CLR_N), UC7.11 (2K), UC7.13 (1CLR_N), UC8.1 (1J), UC8.10 (2CLR_N), UD9.5 (3A)
PU_R26: R26.2, UG3.9 (3A), UG3.12 (4A), UG4.4 (1C), UG4.5 (1D)
PU_R27: R27.2, UE8.9 (2A)
PU_R39: R39.2, UC5.10 (2CLR_N), UC5.13 (1CLR_N), UD5.1 (1J), UD5.4 (1K), UD5.8 (2J), UD5.11 (2K)
PU_R40: R40.2, UD2.2 (1A), UD2.3 (1B), UD2.5 (2A)
PU_R41: R41.2, UB6.10 (2CLR_N), UB6.13 (1CLR_N)
PU_R43: R43.2, UA1.3 (R02)
PU_R44: R44.2, UC1.4 (1PRE_N), UC1.10 (2PRE_N)
PU_R45: R45.2, UC1.1 (1CLR_N), UC1.13 (2CLR_N)
PU_R46: R46.2, UE2.4 (2A)
RA0: UA1.9 (QB), UA2.8 (A0), UB1.10 (2B)
RA1: UA1.8 (QC), UA2.7 (A1), UB1.12 (2C)
RA2: UA1.11 (QD), UA2.6 (A2), UB1.9 (2A), UE8.12 (2C)
RAM0_N: UI8.8 (CS_N), UI9.4 (1Y0_N), UJ8.8 (CS_N)
RAM1_N: UI7.8 (CS_N), UI9.5 (1Y1_N), UJ7.8 (CS_N)
RAM2_N: UI6.8 (CS_N), UI9.6 (1Y2_N), UJ6.8 (CS_N)
RAM3_N: UI5.8 (CS_N), UI9.7 (1Y3_N), UJ5.8 (CS_N)
RAM4_N: UI4.8 (CS_N), UI9.12 (2Y0_N), UJ4.8 (CS_N)
RAM5_N: UI3.8 (CS_N), UI9.11 (2Y1_N), UJ3.8 (CS_N)
RAM6_N: UI2.8 (CS_N), UI9.10 (2Y2_N), UJ2.8 (CS_N)
RAM7_N: UI1.8 (CS_N), UI9.9 (2Y3_N), UJ1.8 (CS_N)
RAMSEL: UG3.3 (1Y), UG3.4 (2A)
RAM_READ_N: UG3.6 (2Y), UH8.19 (2OE_N), UH9.19 (2OE_N)
RDY: R14.2, UF3.2 (RDY)
RES_N: R99.2, UA5.34 (RES_N), UB8.34 (RES_N), UDE9.1 (RST_N), UE4.13 (6A), UF3.40 (RES_N), UG8.34 (RES_N)
REV: UC1.9 (2Q), UC2.1 (1A)
REV_D: UC1.5 (1Q), UC1.12 (2D)
REV_N: UC1.8 (2Q_N), UC2.4 (2A)
ROW0: J5.1 (ROW0), UG9.1 (Y0_N)
ROW1: J5.2 (ROW1), UG9.2 (Y1_N)
ROW2: J5.3 (ROW2), UG9.3 (Y2_N)
ROW3: J5.4 (ROW3), UG9.4 (Y3_N)
ROW4: J5.5 (ROW4), UG9.5 (Y4_N)
ROW5: J5.6 (ROW5), UG9.6 (Y5_N)
ROW6: J5.7 (ROW6), UG9.7 (Y6_N)
ROW7: J5.8 (ROW7), UG9.9 (Y7_N)
ROW7_N: UB1.8 (2Y), UC2.10 (3B)
ROW8: J5.9 (ROW8), UG9.10 (Y8_N)
ROW9: J5.10 (ROW9), UG9.11 (Y9_N)
RW: UA5.22 (RW), UB8.21 (RW), UF3.34 (RW), UG4.2 (1B), UG8.21 (RW)
RW_E: UC2.13 (4B), UG3.5 (2B), UG4.6 (1Y), UG4.9 (2A), UJ9.1 (1A), UJ9.2 (1B)
RW_E_INV: UJ9.3 (1Y), UJ9.4 (2A)
RW_RAM: UD2.6 (2B), UH8.1 (1OE_N), UH9.1 (1OE_N), UI1.10 (WE_N), UI2.10 (WE_N), UI3.10 (WE_N), UI4.10 (WE_N), UI5.10 (WE_N), UI6.10 (WE_N), UI7.10 (WE_N), UI8.10 (WE_N), UJ1.10 (WE_N), UJ2.10 (WE_N), UJ3.10 (WE_N), UJ4.10 (WE_N), UJ5.10 (WE_N), UJ6.10 (WE_N), UJ7.10 (WE_N), UJ8.10 (WE_N), UJ9.6 (2Y)
SA0: UC3.5 (A0), UC4.5 (A0), UD2.9 (3Y)
SA1: UC3.6 (A1), UC4.6 (A1), UD2.12 (4Y)
SA2: UC3.7 (A2), UC4.7 (A2), UD3.4 (1Y)
SA3: UC3.4 (A3), UC4.4 (A3), UD3.7 (2Y)
SA4: UC3.3 (A4), UC4.3 (A4), UD3.9 (3Y)
SA5: UC3.2 (A5), UC4.2 (A5), UD3.12 (4Y)
SA6: UC3.1 (A6), UC4.1 (A6), UD4.4 (1Y)
SA7: UC3.17 (A7), UC4.17 (A7), UD4.7 (2Y)
SA8: UC3.16 (A8), UC4.16 (A8), UD4.9 (3Y)
SA9: UC3.15 (A9), UC4.15 (A9), UD4.12 (4Y)
SD0: UA2.5 (A3), UB3.2 (1A1), UB3.3 (2Y4), UC3.14 (IO1)
SD1: UA2.4 (A4), UB3.4 (1A2), UB3.5 (2Y3), UC3.13 (IO2)
SD2: UA2.3 (A5), UB3.6 (1A3), UB3.7 (2Y2), UC3.12 (IO3)
SD3: UA2.2 (A6), UB3.8 (1A4), UB3.9 (2Y1), UC3.11 (IO4)
SD4: UA2.1 (A7), UB4.2 (1A1), UB4.3 (2Y4), UC4.14 (IO1)
SD5: UA2.23 (A8), UB4.4 (1A2), UB4.5 (2Y3), UC4.13 (IO2)
SD6: UA2.22 (A9), UB4.6 (1A3), UB4.7 (2Y2), UC4.12 (IO3)
SD7: UB4.8 (1A4), UB4.9 (2Y1), UC1.2 (1D), UC4.11 (IO4)
SEL0_N: UG2.1 (Y0_N), UG3.1 (1A), UI9.1 (1G_N)
SEL1_N: UG2.2 (Y1_N), UG3.2 (1B), UI9.15 (2G_N)
SEL8: UC2.12 (4A), UD2.1 (S), UD3.1 (S), UD4.1 (S), UE5.8 (4Y)
SEL8_N: UE5.9 (4A), UG2.9 (Y8_N)
SELC_N: UG2.14 (Y12_N), UG4.10 (2B), UH1.20 (CS1), UH5.20 (CS1)
SELD_N: UG2.15 (Y13_N), UG4.12 (2C), UH2.20 (CS1), UH6.20 (CS1)
SELE_N: UA5.23 (CS2_N), UB8.23 (CS2_N), UG2.16 (Y14_N), UG4.1 (1A), UG8.23 (CS2_N), UH3.20 (CS1)
SELF_N: UG2.17 (Y15_N), UG4.13 (2D), UH4.20 (CS1), UH7.20 (CS1)
SRQ_N: J1.19 (SRQ_N), J2.5 (SRQ_N), UB8.18 (CB1)
SYNC_N: UE5.12 (6Y), UE8.13 (2D)
TA0: UD2.11 (3A), UD5.5 (2Q), UD5.12 (1CLK)
TA1: UD2.14 (4A), UD5.3 (1Q), UD6.8 (CLK1)
TA2: UD3.2 (1A), UD6.5 (QA), UD6.6 (CLK2), UE6.2 (1D1)
TA3: UD3.5 (2A), UD6.9 (QB), UE6.3 (1D2)
TA4: UD3.11 (3A), UD6.2 (QC), UE6.22 (1D3)
TA5: UD3.14 (4A), UD6.12 (QD), UD7.8 (CLK1), UE6.21 (1D4)
TA6: UD4.2 (1A), UD7.5 (QA), UD7.6 (CLK2), UE6.11 (2D1), UE8.10 (2B)
TA7: UD4.5 (2A), UD7.9 (QB), UE6.10 (2D2)
TA8: UD4.11 (3A), UD7.2 (QC), UE6.15 (2D3)
TA9: UD4.14 (4A), UD7.12 (QD), UE6.16 (2D4)
TV_VIDEO: J2.3 (VIDEO), J7.1 (VIDEO_N), UE9.6 (1Y)
USR_CA1: J2.4 (CA1), UA5.40 (CA1)
USR_CB2: J2.22 (CB2), UA5.19 (CB2)
VCC: DS1.2 (A), J3.2 (VCC), J6.2 (VCC), J8.1 (VCC), R10.1, R12.1, R13.1, R14.1, R17.1, R18.1, R19.1, R20.1, R21.1, R22.1, R23.1, R24.1, R25.1, R26.1, R27.1, R28.1, R29.1, R30.1, R31.1, R32.1, R33.1, R34.1, R35.1, R36.1, R37.1, R38.1, R39.1, R40.1, R41.1, R43.1, R44.1, R45.1, R46.1, R48.1, R99.1, UA1.5 (VCC), UA1.14 (CKA), UA2.21 (CS3), UA2.24 (VCC), UA5.20 (VCC), UA7.16 (VCC), UA8.16 (VCC), UA9.16 (VCC), UB1.14 (VCC), UB2.16 (VCC), UB3.20 (VCC), UB4.20 (VCC), UB5.5 (VCC), UB6.14 (VCC), UB8.20 (VCC), UC1.14 (VCC), UC2.14 (VCC), UC3.18 (VCC), UC4.18 (VCC), UC5.14 (VCC), UC6.14 (VCC), UC7.14 (VCC), UC8.14 (VCC), UC9.5 (VCC), UD2.16 (VCC), UD3.16 (VCC), UD4.16 (VCC), UD5.14 (VCC), UD6.14 (VCC), UD7.14 (VCC), UD8.14 (VCC), UD9.14 (VCC), UDE9.8 (VCC), UE2.14 (VCC), UE3.14 (VCC), UE4.14 (VCC), UE5.14 (VCC), UE6.24 (VCC), UE8.14 (VCC), UE9.14 (VCC), UF3.8 (VCC), UF3.38 (SO), UG2.24 (VCC), UG3.14 (VCC), UG4.14 (VCC), UG5.20 (VCC), UG6.20 (VCC), UG8.20 (VCC), UG9.16 (VCC), UH1.21 (CS3), UH1.24 (VCC), UH2.21 (CS3), UH2.24 (VCC), UH3.21 (CS3), UH3.24 (VCC), UH4.21 (CS3), UH4.24 (VCC), UH5.21 (CS3), UH5.24 (VCC), UH6.21 (CS3), UH6.24 (VCC), UH7.21 (CS3), UH7.24 (VCC), UH8.20 (VCC), UH9.20 (VCC), UI1.18 (VCC), UI2.18 (VCC), UI3.18 (VCC), UI4.18 (VCC), UI5.18 (VCC), UI6.18 (VCC), UI7.18 (VCC), UI8.18 (VCC), UI9.16 (VCC), UJ1.18 (VCC), UJ2.18 (VCC), UJ3.18 (VCC), UJ4.18 (VCC), UJ5.18 (VCC), UJ6.18 (VCC), UJ7.18 (VCC), UJ8.18 (VCC), UJ9.14 (VCC), X1.14 (VCC)
VEND: UC6.13 (4B), UD8.6 (2Y)
VERT_DRIVE: J2.19 (VERT), J7.3 (VDRIVE), UD8.11 (4Y)
VIA_CS1: UA5.24 (CS1), UE2.8 (3Y)
VIDEO_ON: UA5.15 (PB5), UC6.8 (3Y), UE5.13 (6A), UE9.2 (1B), UG8.18 (CB1)
VREAD_N: UB3.1 (1OE_N), UB4.1 (1OE_N), UC2.11 (4Y)
VRW_N: UB3.19 (2OE_N), UB4.19 (2OE_N), UC3.10 (WE_N), UC4.10 (WE_N), UD2.7 (2Y)
VS0: UB6.3 (1Q), UB6.8 (2J), UC6.9 (3A)
VS0_N: UB6.2 (1Q_N), UB6.11 (2K), UD8.13 (4B)
VS1: UB6.4 (1K), UB6.5 (2Q), UC6.10 (3B)
VS1_N: UB6.1 (1J), UB6.6 (2Q_N), UD8.12 (4A)
VSTEP: UA1.2 (R01), UB6.9 (2CLK), UB6.12 (1CLK), UC7.3 (1Q)
VSTEP_J: UC6.11 (4Y), UC7.1 (1J)
VSTEP_N: UC2.9 (3A), UC7.2 (1Q_N), UD6.13 (CLR_N), UD7.13 (CLR_N)

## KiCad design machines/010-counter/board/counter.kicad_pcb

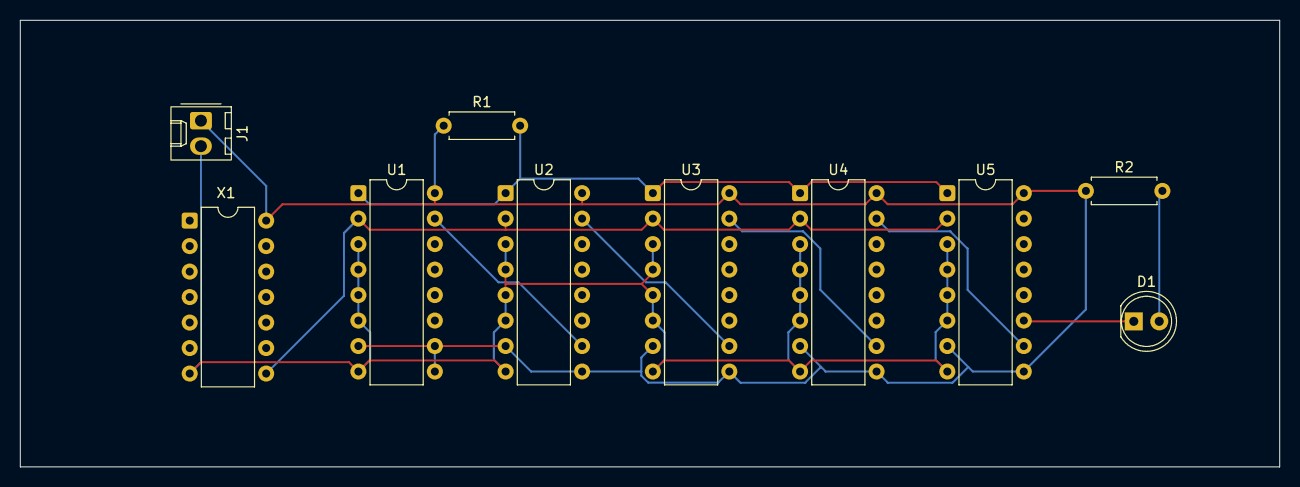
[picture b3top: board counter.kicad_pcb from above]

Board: 2 copper layers, 125.5 x 44.5 mm, 10 parts (0 on the bottom side), 10 nets.

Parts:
D1: LED; LED_D5.0mm
J1: POWER; Molex_KK-254_AE-6410-02A_1x02_P2.54mm_Vertical
R1: 4k7; R_Axial_DIN0207_L6.3mm_D2.5mm_P7.62mm_Horizontal
R2: 330; R_Axial_DIN0207_L6.3mm_D2.5mm_P7.62mm_Horizontal
U1, U2, U3, U4, U5: 74LS161; DIP-16_W7.62mm
X1: OSC; DIP-14_W7.62mm

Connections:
C19: D1.1 (K), U5.11 (QD)
CARRY1: U1.15 (RCO), U2.10 (ENT)
CARRY2: U2.15 (RCO), U3.10 (ENT)
CARRY3: U3.15 (RCO), U4.10 (ENT)
CARRY4: U4.15 (RCO), U5.10 (ENT)
CLK: U1.2 (CLK), U2.2 (CLK), U3.2 (CLK), U4.2 (CLK), U5.2 (CLK), X1.8 (OUT)
GND: J1.2 (GND), U1.3 (A), U1.4 (B), U1.5 (C), U1.6 (D), U1.8 (GND), U2.3 (A), U2.4 (B), U2.5 (C), U2.6 (D), U2.8 (GND), U3.3 (A), U3.4 (B), U3.5 (C), U3.6 (D), U3.8 (GND), U4.3 (A), U4.4 (B), U4.5 (C), U4.6 (D), U4.8 (GND), U5.3 (A), U5.4 (B), U5.5 (C), U5.6 (D), U5.8 (GND), X1.7 (GND)
LED_A: D1.2 (A), R2.2
RESET_N: R1.2, U1.1 (CLR_N), U2.1 (CLR_N), U3.1 (CLR_N), U4.1 (CLR_N), U5.1 (CLR_N)
VCC: J1.1 (VCC), R1.1, R2.1, U1.7 (ENP), U1.9 (LOAD_N), U1.10 (ENT), U1.16 (VCC), U2.7 (ENP), U2.9 (LOAD_N), U2.16 (VCC), U3.7 (ENP), U3.9 (LOAD_N), U3.16 (VCC), U4.7 (ENP), U4.9 (LOAD_N), U4.16 (VCC), U5.7 (ENP), U5.9 (LOAD_N), U5.16 (VCC), X1.14 (VCC)
